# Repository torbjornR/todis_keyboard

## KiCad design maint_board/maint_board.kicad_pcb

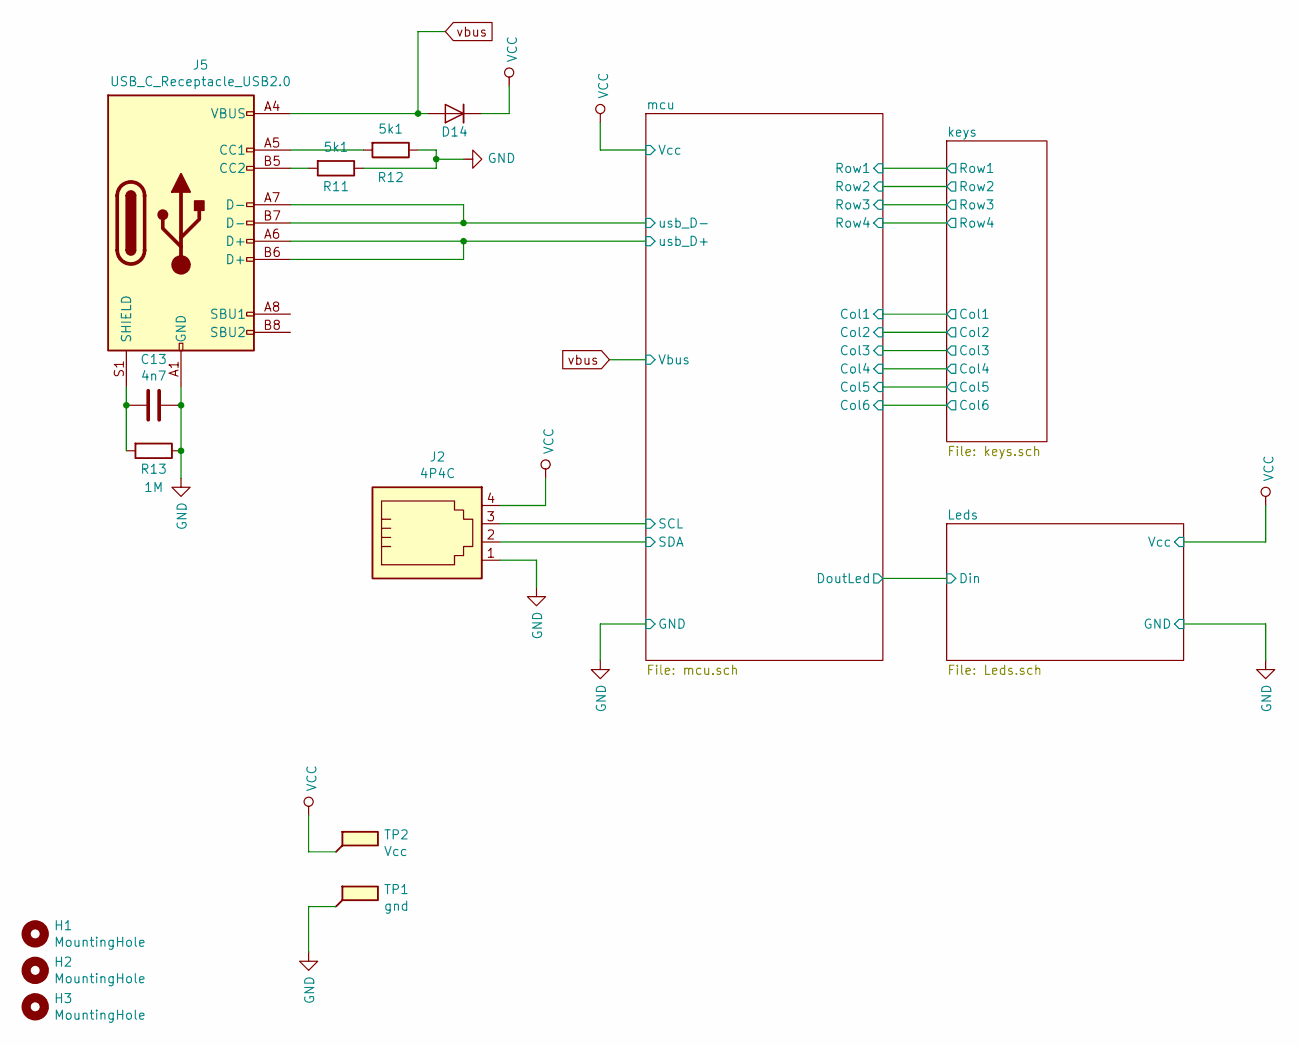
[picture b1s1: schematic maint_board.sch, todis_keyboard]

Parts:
C13: 4n7; C_1608
D14: 1N4148W; D_SOD-323
H1, H2, H3: MountingHole; MountingHole_2.2mm_M2_ISO7380
J2: 4P4C; glx-n-44_reverseble
J5: USB_C_Receptacle_USB2.0; USB_C_Receptacle_Palconn_UTC16-G
R11, R12: 5k1; R_0603_1608Metric_Pad1.05x0.95mm_HandSolder
R13: 1M; R_0603_1608Metric_Pad1.05x0.95mm_HandSolder
TP1: gnd; TestPoint_Pad_1.5x1.5mm
TP2: Vcc; TestPoint_Pad_1.5x1.5mm

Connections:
/mcu/SCL: J2.3; also elsewhere on the board
/mcu/SDA: J2.2; also elsewhere on the board
/mcu/usb_D+: J5.A6 (D+), J5.B6 (D+); also elsewhere on the board
/mcu/usb_D-: J5.A7 (D-), J5.B7 (D-); also elsewhere on the board
GND: C13.1, J2.1, J5.A1 (GND), J5.A12 (GND), J5.B1 (GND), J5.B12 (GND), R11.1, R12.1, R13.1, TP1.1; also elsewhere on the board
unnamed: C13.2, J5.S1 (SHIELD), R13.2
unnamed: J5.A5 (CC1), R12.2
unnamed: J5.B5 (CC2), R11.2
VCC: D14.1 (K), J2.4, TP2.1; also elsewhere on the board
vbus: D14.2 (A), J5.A4 (VBUS), J5.A9 (VBUS), J5.B4 (VBUS), J5.B9 (VBUS); also elsewhere on the board

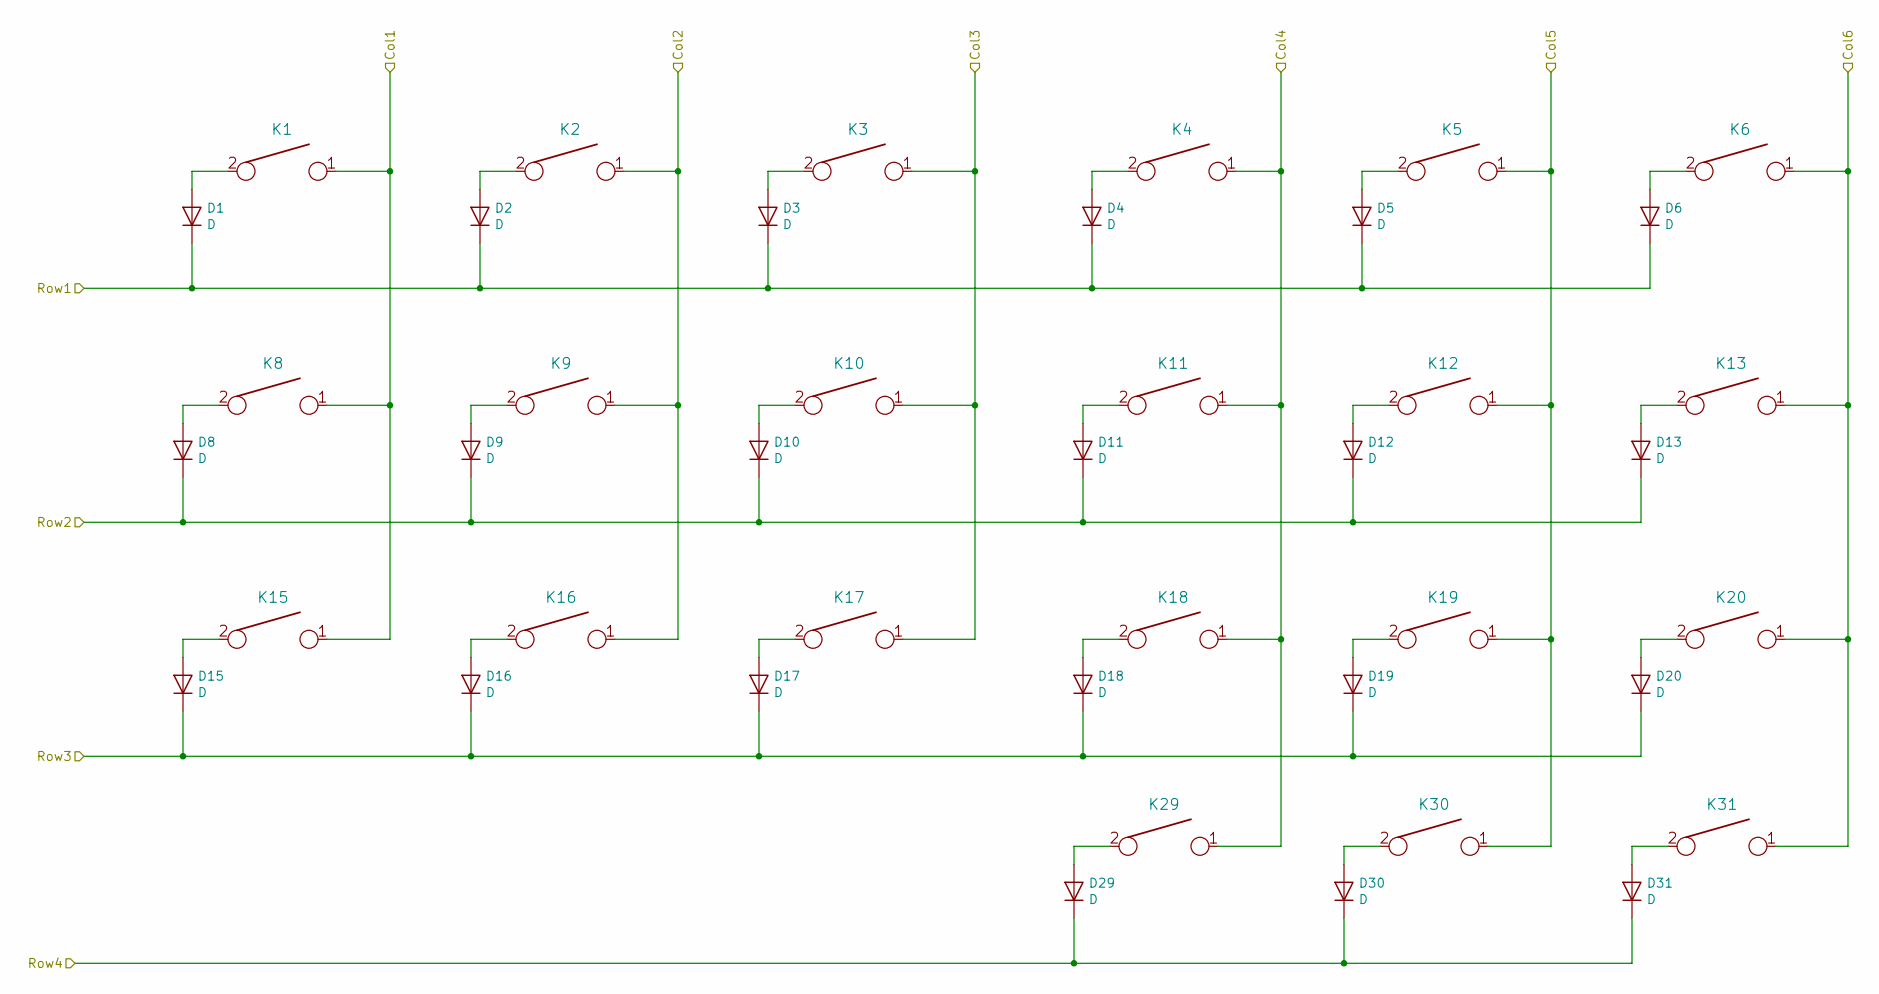
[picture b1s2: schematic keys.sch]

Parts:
D1, D2, D3, D4, D5, D6, D8, D9, D10, D11, D12, D13, D15, D16, D17, D18, D19, D20, D29, D30, D31: D; D_SOD123_axial
K1, K2, K3, K4, K5, K6, K8, K9, K10, K11, K12, K13, K15, K16, K17, K18, K19, K20, K29, K30, K31: KEYSW; SW_MX_reversible

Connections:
/keys/Col1: K1.1, K8.1, K15.1; also elsewhere on the board
/keys/Col2: K2.1, K9.1, K16.1; also elsewhere on the board
/keys/Col3: K3.1, K10.1, K17.1; also elsewhere on the board
/keys/Col4: K4.1, K11.1, K18.1, K29.1; also elsewhere on the board
/keys/Col5: K5.1, K12.1, K19.1, K30.1; also elsewhere on the board
/keys/Col6: K6.1, K13.1, K20.1, K31.1; also elsewhere on the board
/keys/Row1: D1.1 (K), D2.1 (K), D3.1 (K), D4.1 (K), D5.1 (K), D6.1 (K); also elsewhere on the board
/keys/Row2: D8.1 (K), D9.1 (K), D10.1 (K), D11.1 (K), D12.1 (K), D13.1 (K); also elsewhere on the board
/keys/Row3: D15.1 (K), D16.1 (K), D17.1 (K), D18.1 (K), D19.1 (K), D20.1 (K); also elsewhere on the board
/keys/Row4: D29.1 (K), D30.1 (K), D31.1 (K); also elsewhere on the board
unnamed: D1.2 (A), K1.2
unnamed: D2.2 (A), K2.2
unnamed: D3.2 (A), K3.2
unnamed: D4.2 (A), K4.2
unnamed: D5.2 (A), K5.2
unnamed: D6.2 (A), K6.2
unnamed: D8.2 (A), K8.2
unnamed: D9.2 (A), K9.2
unnamed: D10.2 (A), K10.2
unnamed: D11.2 (A), K11.2
unnamed: D12.2 (A), K12.2
unnamed: D13.2 (A), K13.2
unnamed: D15.2 (A), K15.2
unnamed: D16.2 (A), K16.2
unnamed: D17.2 (A), K17.2
unnamed: D18.2 (A), K18.2
unnamed: D19.2 (A), K19.2
unnamed: D20.2 (A), K20.2
unnamed: D29.2 (A), K29.2
unnamed: D30.2 (A), K30.2
unnamed: D31.2 (A), K31.2

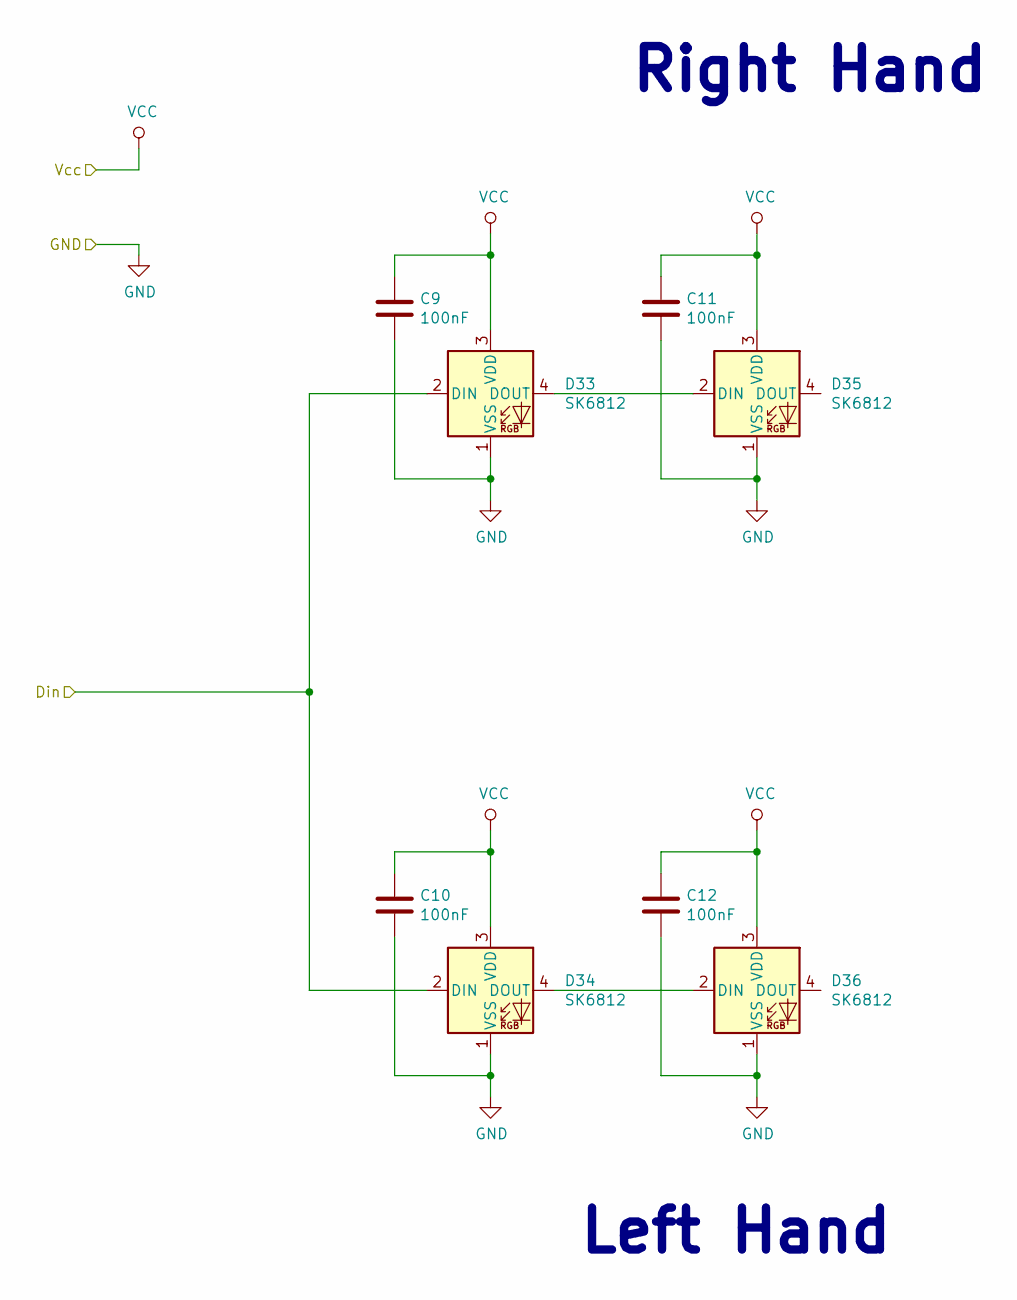
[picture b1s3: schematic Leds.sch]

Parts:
C9, C10, C11, C12: 100nF; C_1608
D33, D34, D35, D36: SK6812; LED_SK6812_PLCC4_5.0x5.0mm_P3.2mm

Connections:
/Leds/Din: D33.2 (DIN), D34.2 (DIN); also elsewhere on the board
GND: C9.2, C10.2, C11.2, C12.2, D33.1 (VSS), D34.1 (VSS), D35.1 (VSS), D36.1 (VSS); also elsewhere on the board
unnamed: D33.4 (DOUT), D35.2 (DIN)
unnamed: D34.4 (DOUT), D36.2 (DIN)
VCC: C9.1, C10.1, C11.1, C12.1, D33.3 (VDD), D34.3 (VDD), D35.3 (VDD), D36.3 (VDD); also elsewhere on the board

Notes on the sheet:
Left Hand
Right Hand

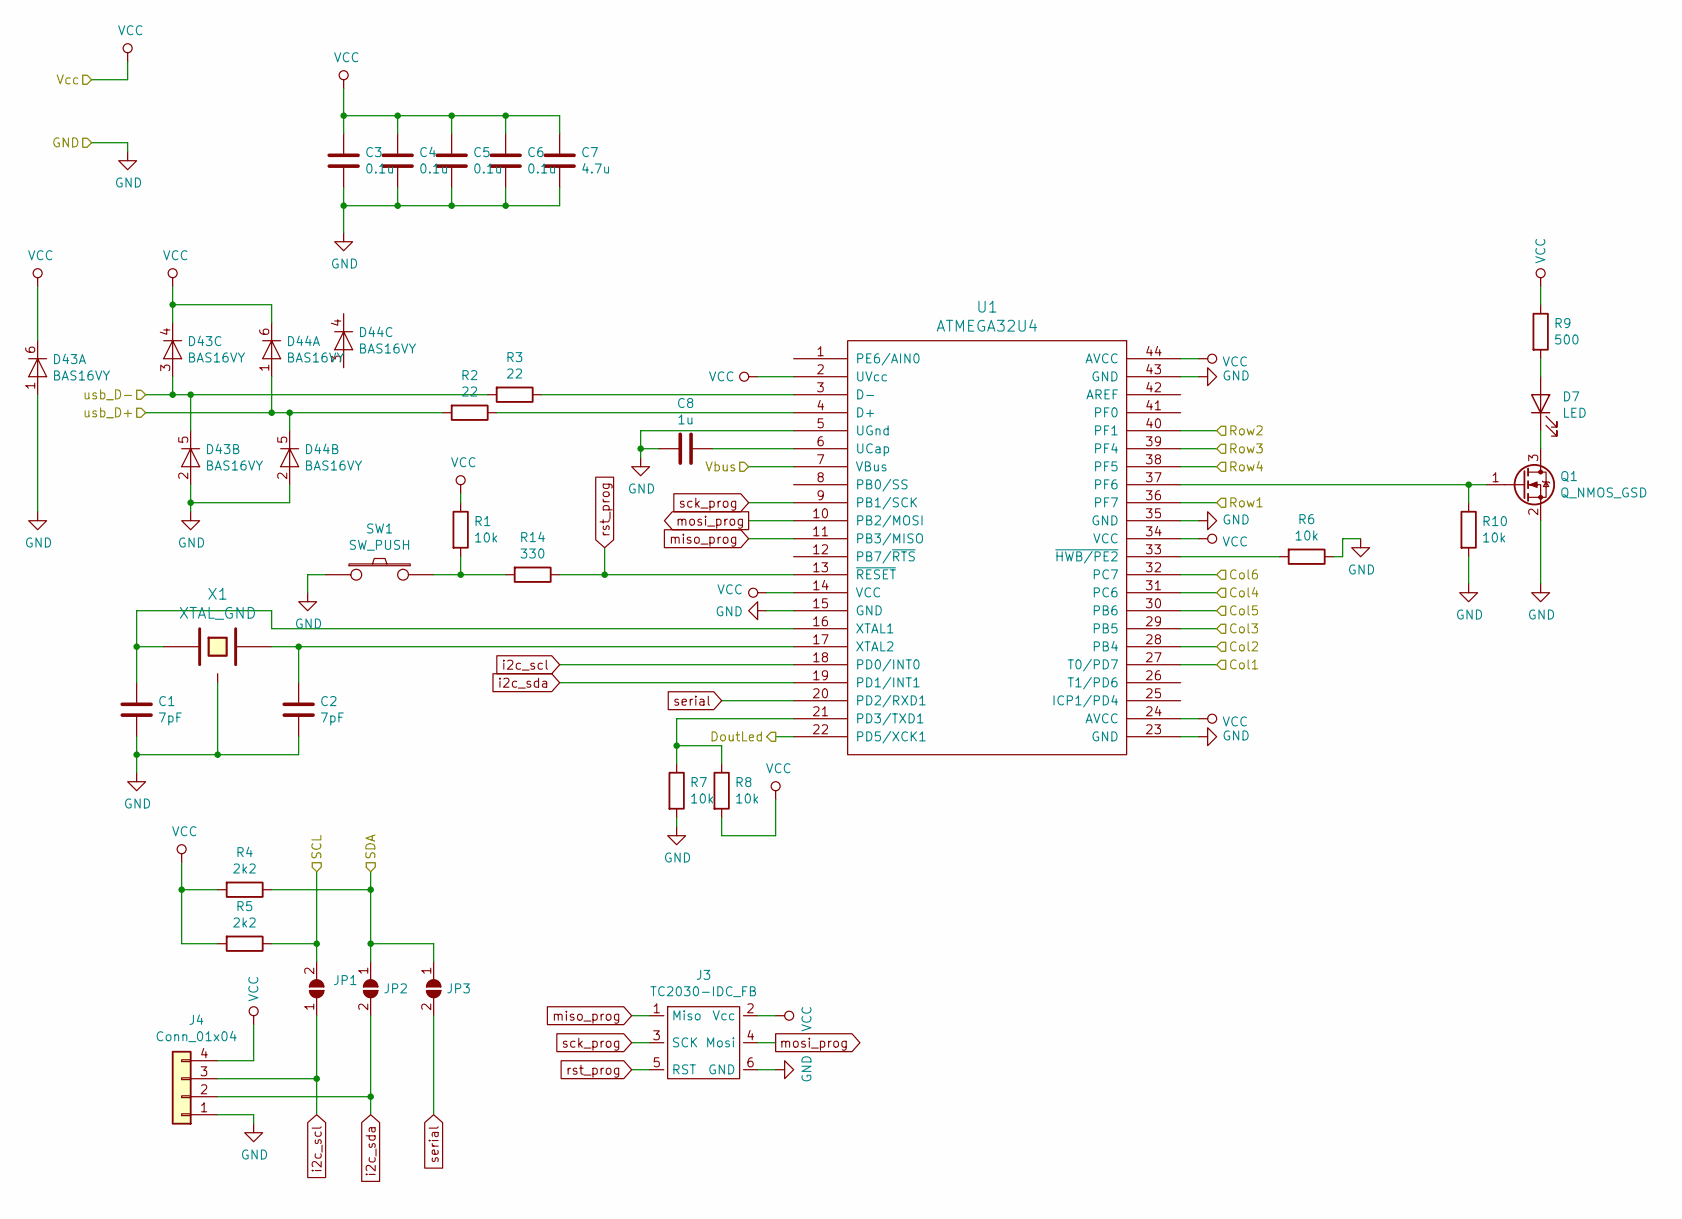
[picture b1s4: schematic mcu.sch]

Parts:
C1, C2: 7pF; C_1608
C3, C4, C5, C6: 0.1u; C_1608
C7: 4.7u; C_1608
C8: 1u; C_1608
D7: LED; D_0603_1608Metric
D43, D44: BAS16VY; SOT-363_SC-70-6
J3: TC2030-IDC_FB; Tag-Connect_TC2030-IDC-NL_2x03_P1.27mm_Vertical
J4: Conn_01x04; PinHeader_1x04_P1.00mm_Vertical
JP1, JP2, JP3: SolderJumper_2_Open; SolderJumper-2_P1.3mm_Open_RoundedPad1.0x1.5mm
Q1: Q_NMOS_GSD; SOT-23
R1, R6, R7, R8, R10: 10k; R_0603_1608Metric_Pad1.05x0.95mm_HandSolder
R2, R3: 22; R_0603_1608Metric_Pad1.05x0.95mm_HandSolder
R4, R5: 2k2; R_0603_1608Metric_Pad1.05x0.95mm_HandSolder
R9: 500; R_0603_1608Metric_Pad1.05x0.95mm_HandSolder
R14: 330; R_0603_1608Metric_Pad1.05x0.95mm_HandSolder
SW1: SW_PUSH; SW_SPST_B3U-1000P
U1: ATMEGA32U4; QFP44
X1: XTAL_GND; FA-238

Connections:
/Leds/Din: U1.22 (PD5/XCK1); also elsewhere on the board
/keys/Col1: U1.27 (T0/PD7); also elsewhere on the board
/keys/Col2: U1.28 (PB4); also elsewhere on the board
/keys/Col3: U1.29 (PB5); also elsewhere on the board
/keys/Col4: U1.31 (PC6); also elsewhere on the board
/keys/Col5: U1.30 (PB6); also elsewhere on the board
/keys/Col6: U1.32 (PC7); also elsewhere on the board
/keys/Row1: U1.36 (PF7); also elsewhere on the board
/keys/Row2: U1.40 (PF1); also elsewhere on the board
/keys/Row3: U1.39 (PF4); also elsewhere on the board
/keys/Row4: U1.38 (PF5); also elsewhere on the board
/mcu/SCL: JP1.2 (B), R5.1; also elsewhere on the board
/mcu/SDA: JP2.1 (A), JP3.1 (A), R4.1; also elsewhere on the board
/mcu/usb_D+: D44.1 (A), D44.5 (K), R2.2; also elsewhere on the board
/mcu/usb_D-: D43.3 (A), D43.5 (K), R3.2; also elsewhere on the board
GND: C1.2, C2.2, C3.2, C4.2, C5.2, C6.2, C7.2, C8.2, D43.1 (A), D43.2 (A), D44.2 (A), J3.6 (GND), J4.1, Q1.2 (S), R6.1, R7.2, R10.2, SW1.1, U1.5 (UGnd), U1.15 (GND), U1.23 (GND), U1.35 (GND), U1.43 (GND), X1.3; also elsewhere on the board
unnamed: C1.1, U1.16 (XTAL1), X1.1
unnamed: C2.1, U1.17 (XTAL2), X1.2
unnamed: C8.1, U1.6 (UCap)
unnamed: D7.1 (K), Q1.3 (D)
unnamed: D7.2 (A), R9.2
unnamed: Q1.1 (G), R10.1, U1.37 (PF6)
unnamed: R1.2, R14.2, SW1.2
unnamed: R2.1, U1.4 (D+)
unnamed: R3.1, U1.3 (D-)
unnamed: R6.2, U1.33 (~HWB/PE2)
unnamed: R7.1, R8.1, U1.21 (PD3/TXD1)
VCC: C3.1, C4.1, C5.1, C6.1, C7.1, D43.4 (K), D43.6 (K), D44.6 (K), J3.2 (Vcc), J4.4, R1.1, R4.2, R5.2, R8.2, R9.1, U1.2 (UVcc), U1.14 (VCC), U1.24 (AVCC), U1.34 (VCC), U1.44 (AVCC); also elsewhere on the board
i2c_scl: J4.3, JP1.1 (A), U1.18 (PD0/INT0)
i2c_sda: J4.2, JP2.2 (B), U1.19 (PD1/INT1)
miso_prog: J3.1 (Miso), U1.11 (PB3/MISO)
mosi_prog: J3.4 (Mosi), U1.10 (PB2/MOSI)
rst_prog: J3.5 (RST), R14.1, U1.13 (~RESET)
sck_prog: J3.3 (SCK), U1.9 (PB1/SCK)
serial: JP3.2 (B), U1.20 (PD2/RXD1)
vbus: U1.7 (VBus); also elsewhere on the board

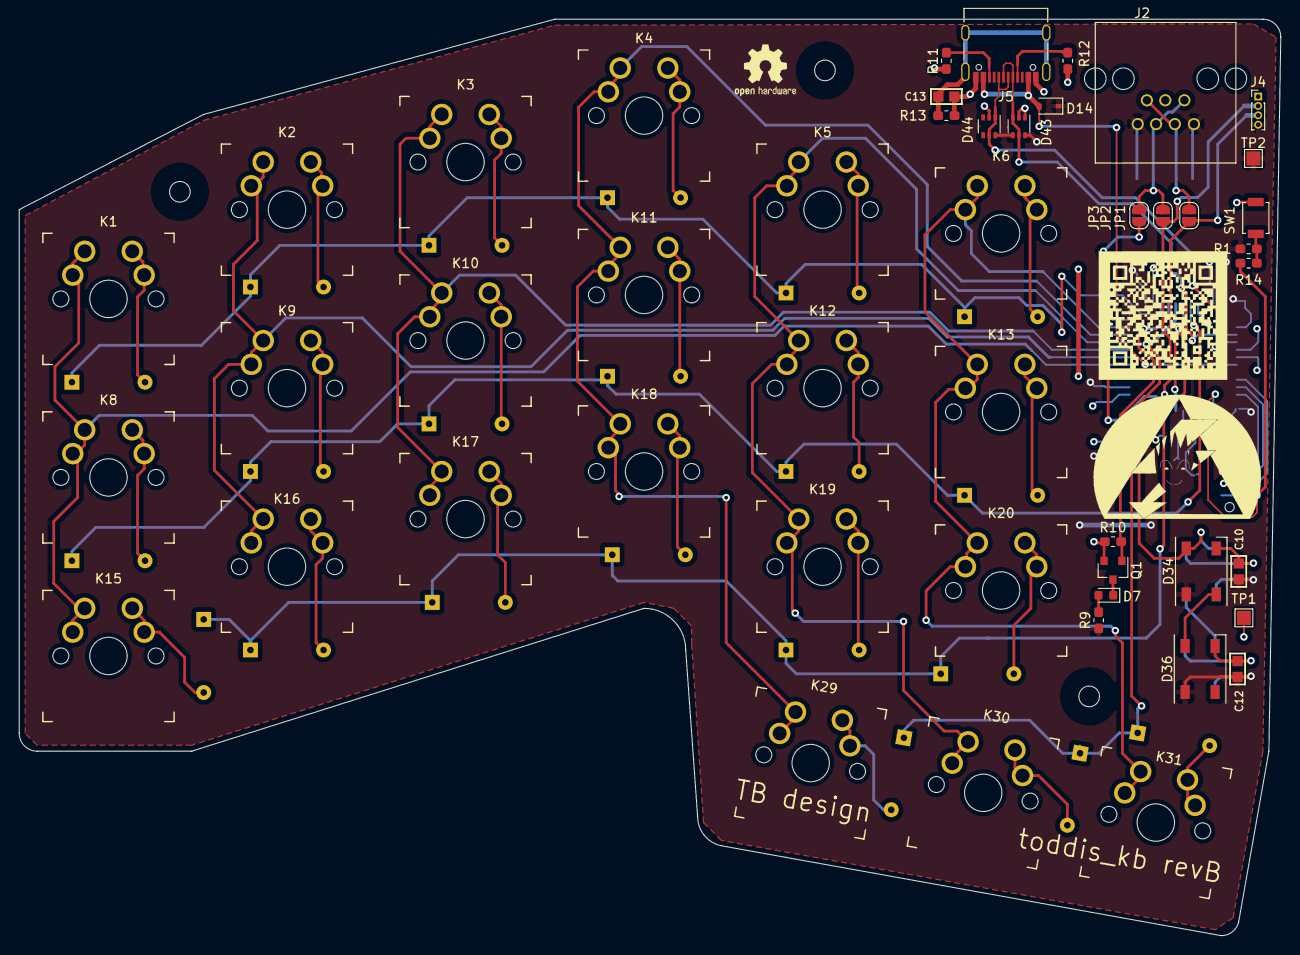
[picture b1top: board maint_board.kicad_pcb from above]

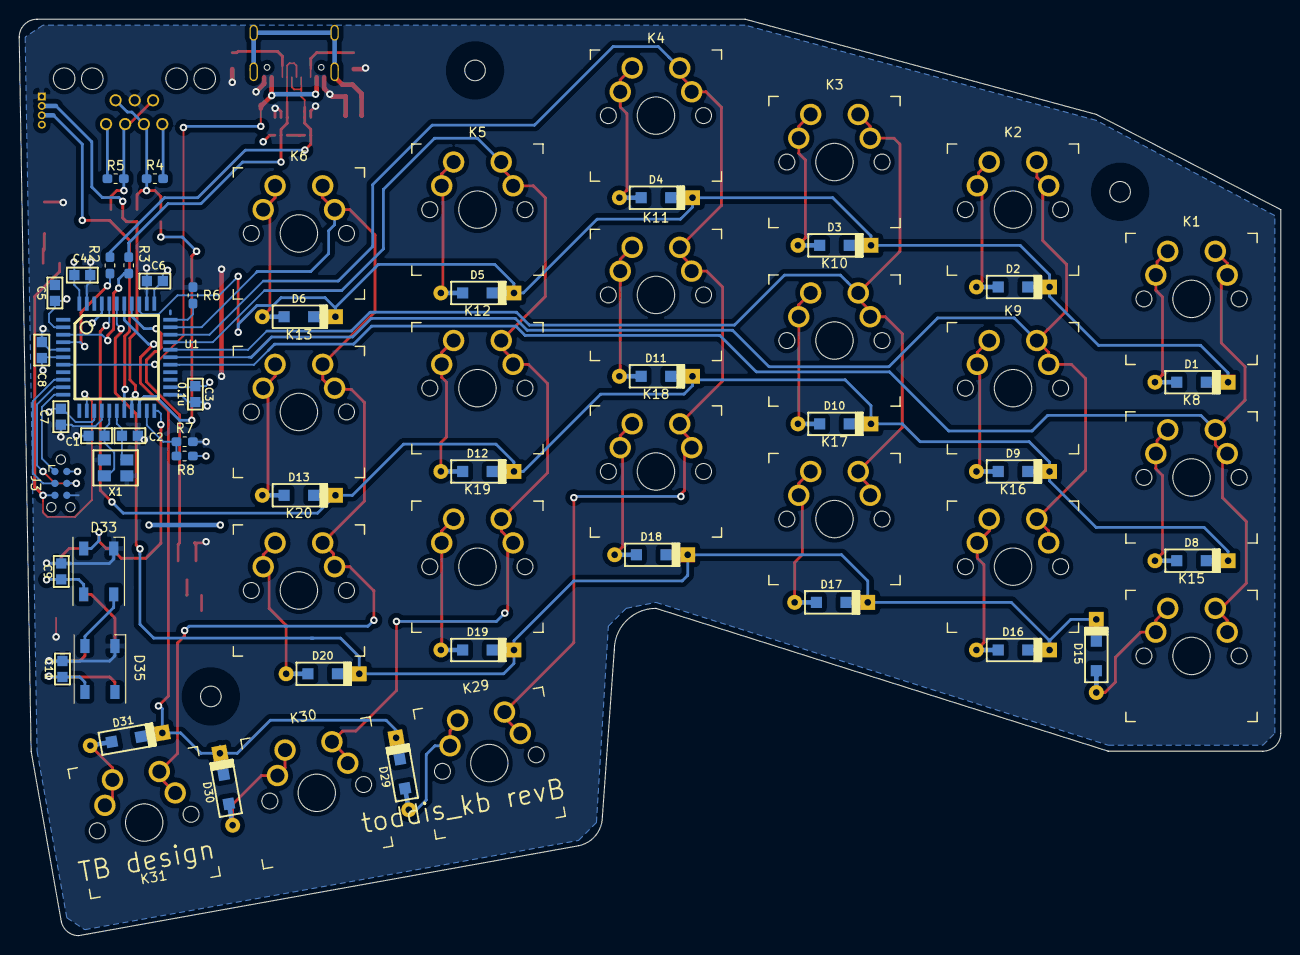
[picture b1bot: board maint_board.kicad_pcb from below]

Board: 2 copper layers, 134.6 x 97.8 mm, 93 parts (43 on the bottom side), 62 nets.

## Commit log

2021-03-09 added dcm
2021-03-09 addad chace.lib
2021-03-09 added lib submodule
2021-03-09 added the pcb files
2021-03-10 added libs and worked on layout
2021-03-31 Finiched!
2021-03-31 Added mounting holes
2021-04-04 Added silc art and rounded corners
2021-04-05 added silk art and cleand upp copper pour
2021-04-06 Fixed the board outline it was not one consistent line
2021-05-28 commit before reinstall computer
2021-05-30 added some libs in case they are needed
2021-11-03 updated submodule
2021-11-14 removed two leds and fixed recet and usb port
2021-11-19 this is before I switch to usb C
2021-11-20 added filter on usb shield
2021-12-02 added som libes
2021-12-13 added submodules fore two firmware branches
2021-12-15 added schematic in pdf form
2022-10-30 safty coppy before reinstall of computer
